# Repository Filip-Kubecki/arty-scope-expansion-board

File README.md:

<!-- markdownlint-disable MD013 MD060 -->

# Two-Channel Scope Expansion Board for Arty A7

KiCad design of an analog shield for the Digilent Arty A7 100T. The board plugs into the Pmod connectors and, together with the FPGA design, forms a two-channel digital oscilloscope.

## Hardware

- **Host board:** Digilent Arty A7 100T (connected via Pmod headers)
- **ADC:** AD9288-100 (dual 8-bit, 100 MS/s)
- **PGA:** AD8370 (variable gain amplifier)
- **DAC:** MCP4822 (DC offset)
- **EDA:** KiCad 10.0

## Related repositories

- FPGA design: [arty-scope-hdl](https://github.com/Filip-Kubecki/arty-scope-hdl)

## Repository structure

```
hardware/      KiCad project (schematic, PCB, project-local libraries)
  libs/        custom symbols, footprints and 3D models
docs/          notes, datasheets, pinout and block diagram
fab/           fabrication outputs - Gerbers, drill, BOM, pick&place (git-ignored, see Releases)
```

## Getting started

Clone the repository:

```bash
git clone https://github.com/Filip-Kubecki/arty-scope-expansion-board.git
cd arty-scope-expansion-board
```

Open `hardware/arty-scope-expansion-board.kicad_pro` in KiCad. Project-local libraries are referenced through `sym-lib-table` and `fp-lib-table`, so no manual setup is needed.

### Generating fabrication files

Fabrication outputs are not stored in git. To generate them:

1. Open the PCB in the PCB Editor.
2. Run **File → Fabrication Outputs → Gerbers** and **Drill Files**, writing to `fab/`.
3. Export BOM and placement files from the Schematic and PCB Editors if needed.

Ready-to-order packages for tagged versions are attached to [GitHub Releases](https://github.com/Filip-Kubecki/arty-scope-expansion-board/releases).

## Status

Work in progress.

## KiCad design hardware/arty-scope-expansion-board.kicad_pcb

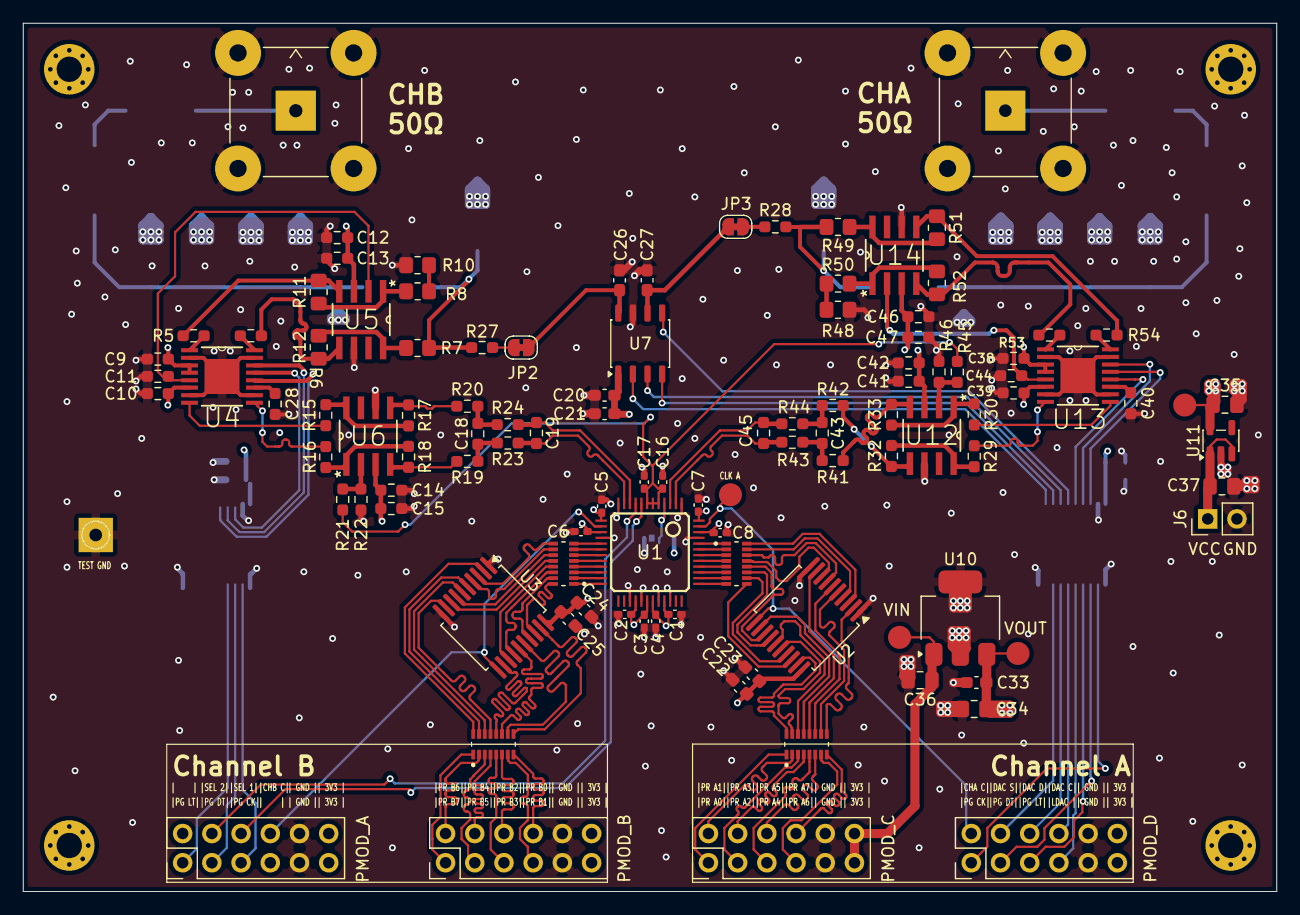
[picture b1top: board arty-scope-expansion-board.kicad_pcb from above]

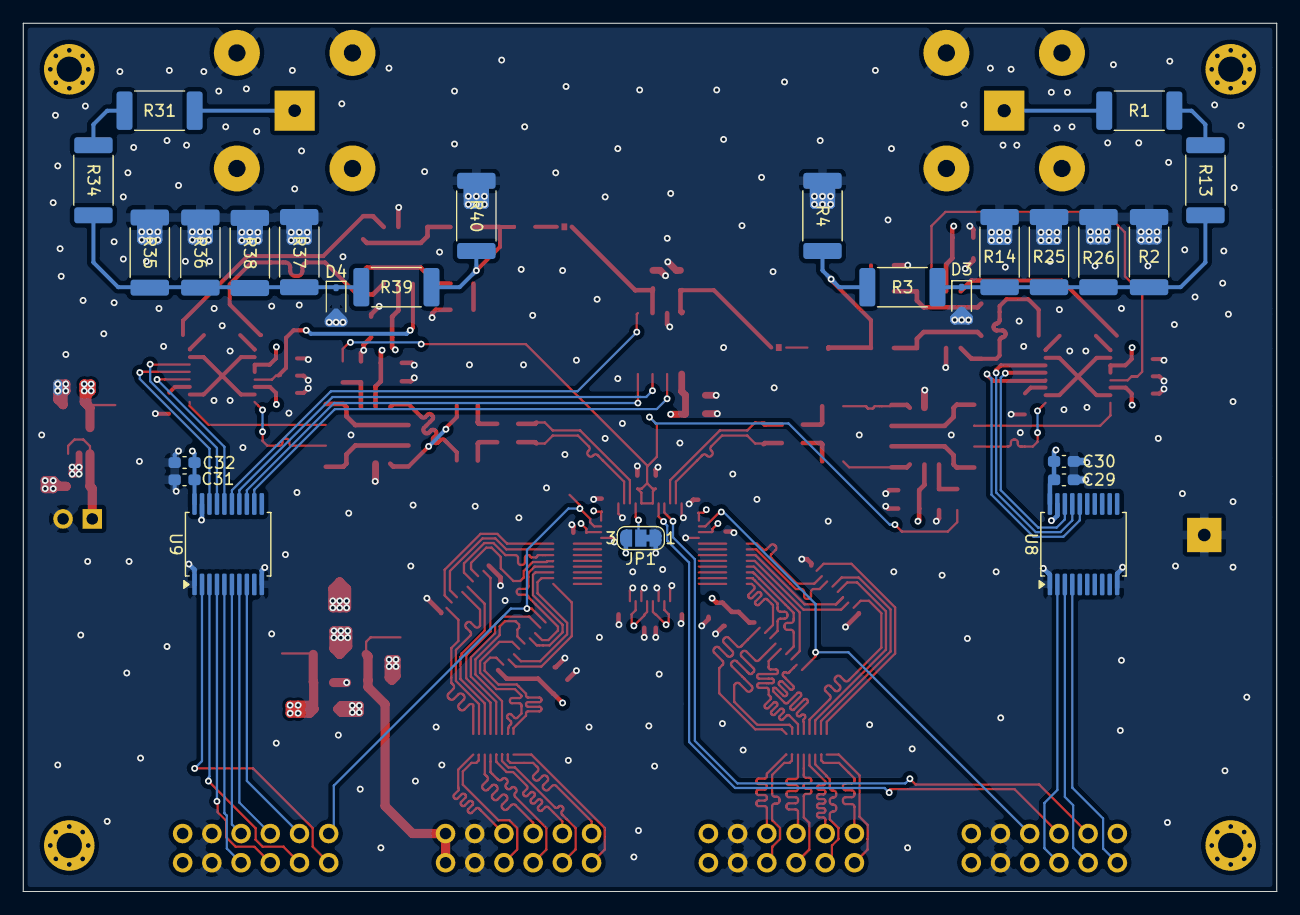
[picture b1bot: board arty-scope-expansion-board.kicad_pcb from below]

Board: 4 copper layers, 109.0 x 75.5 mm, 129 parts (25 on the bottom side), 147 nets.

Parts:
C1, C2, C3, C4, C5, C6, C7, C8, C16, C17: 100n; C_0402_1005Metric_Pad0.74x0.62mm_HandSolder
C9, C13, C14, C38, C41, C46: 100n; R_0603_1608Metric_Pad0.98x0.95mm_HandSolder
C10, C11, C28, C39, C40, C44: 1n; R_0603_1608Metric_Pad0.98x0.95mm_HandSolder
C12, C15, C42, C47: 10u; R_0603_1608Metric_Pad0.98x0.95mm_HandSolder
C18, C43: 47p; R_0603_1608Metric_Pad0.98x0.95mm_HandSolder
C19, C45: 10p; R_0603_1608Metric_Pad0.98x0.95mm_HandSolder
C20, C23, C25, C29, C31, C33: 100n; C_0603_1608Metric_Pad1.08x0.95mm_HandSolder
C21, C22, C24, C30, C32: 10u; C_0603_1608Metric_Pad1.08x0.95mm_HandSolder
C26, C27: 1n; C_0603_1608Metric_Pad1.08x0.95mm_HandSolder
C34, C35, C37: 1u; C_0805_2012Metric_Pad1.18x1.45mm_HandSolder
C36: 4u7; C_0805_2012Metric_Pad1.18x1.45mm_HandSolder
D3, D4: CDSOD323-T24C; D_SOD-323
J1: PMOD_A; PinHeader_2x06_P2.54mm_Vertical
J2: PMOD_B; PinHeader_2x06_P2.54mm_Vertical
J3: PMOD_C; PinHeader_2x06_P2.54mm_Vertical
J4: PMOD_D; PinHeader_2x06_P2.54mm_Vertical
J5, J7: Conn_Coaxial; BNC_TEConnectivity_1478035_Horizontal
J6: Conn_01x02_Pin; PinHeader_1x02_P2.54mm_Vertical
JP1: DFS Select; SolderJumper-3_P1.3mm_Bridged12_RoundedPad1.0x1.5mm_NumberL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
JP2, JP3: Jumper_2_Bridged; SolderJumper-2_P1.3mm_Bridged_RoundedPad1.0x1.5mm
R1, R13, R31, R34: 11; R_2512_6332Metric_Pad1.40x3.35mm_HandSolder
R2, R14, R25, R26, R35, R36, R37, R38: 222; R_2512_6332Metric_Pad1.40x3.35mm_HandSolder
R3, R39: 499; R_2512_6332Metric_Pad1.40x3.35mm_HandSolder
R4, R40: 55.6; R_2512_6332Metric_Pad1.40x3.35mm_HandSolder
R5, R6, R19, R20, R41, R42, R53, R54: 100; R_0603_1608Metric_Pad0.98x0.95mm_HandSolder
R7, R8, R11, R12, R49, R50, R51, R52: 499; R_0805_2012Metric_Pad1.20x1.40mm_HandSolder
R10, R48: 27.8; R_0805_2012Metric_Pad1.20x1.40mm_HandSolder
R15, R16, R17, R18, R29, R30, R32, R33: 499; R_0603_1608Metric_Pad0.98x0.95mm_HandSolder
R21, R45: 2.61k; R_0603_1608Metric_Pad0.98x0.95mm_HandSolder
R22, R46: 10k; R_0603_1608Metric_Pad0.98x0.95mm_HandSolder
R23, R24, R43, R44: 49.9; R_0603_1608Metric_Pad0.98x0.95mm_HandSolder
R27, R28: 20k; R_0603_1608Metric_Pad0.98x0.95mm_HandSolder
R_Pack_ADC_Side_A1: 51; RESCAXE50P380X160X55-16N
R_Pack_ADC_Side_B1: 51; RESCAXE50P380X160X55-16N
R_Pack_PMOD_Side_A1: 51; RESCAXE50P380X160X55-16N
R_Pack_PMOD_Side_B1: 51; RESCAXE50P380X160X55-16N
U1: AD9288; LQFP48
U2, U3: 74LS374; SSOP-20_5.3x7.2mm_P0.65mm
U4, U13: AD8370AREZ-RL7; SOP65P640X120-17N
U5, U6, U12, U14: AD8132ARZ; SOIC127P600X175-8N
U7: MCP4822; JEITA_SOIC-8_3.9x4.9mm_P1.27mm
U8, U9: 74AHCT541; SSOP-20_5.3x7.2mm_P0.65mm
U10: MCP1826S; SOT-223-3_TabPin2
U11: MIC5504-3.3YM5; SOT-23-5

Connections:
+3.3VCC: C1.1, C2.1, C3.1, C4.1, C5.1, C6.1, C7.1, C8.1, C22.1, C23.1, C24.1, C25.1, C33.1, C34.1, JP1.3 (B), U1.13 (VD@1), U1.15 (VDD@1), U1.28 (VDD@2), U1.30 (VD@2), U1.31 (VD@3), U1.33 (VDD@3), U1.46 (VDD@4), U1.48 (VD@4), U2.20 (VCC), U3.20 (VCC), U10.3 (VO)
+5VCC: C9.2, C10.2, C12.2, C13.2, C14.2, C15.2, C20.2, C21.2, C29.2, C30.2, C31.2, C32.2, C35.1, C38.2, C39.2, C41.2, C42.2, C46.2, C47.2, U4.3 (VCCI), U4.4 (PWUP), U4.6 (VCCO_2), U5.3 (V+), U6.3 (V+), U7.1 (Vdd), U8.20 (VCC), U9.20 (VCC), U11.5 (VOUT), U12.3 (V+), U13.3 (VCCI), U13.4 (PWUP), U13.6 (VCCO_2), U14.3 (V+)
/Root/ADC_DATA_A0: R_Pack_ADC_Side_A1.8 (R8.1), U1.37 (D0A)
/Root/ADC_DATA_A1: R_Pack_ADC_Side_A1.7 (R7.1), U1.38 (D1A)
/Root/ADC_DATA_A2: R_Pack_ADC_Side_A1.6 (R6.1), U1.39 (D2A)
/Root/ADC_DATA_A3: R_Pack_ADC_Side_A1.5 (R5.1), U1.40 (D3A)
/Root/ADC_DATA_A4: R_Pack_ADC_Side_A1.4 (R4.1), U1.41 (D4A)
/Root/ADC_DATA_A5: R_Pack_ADC_Side_A1.3 (R3.1), U1.42 (D5A)
/Root/ADC_DATA_A6: R_Pack_ADC_Side_A1.2 (R2.1), U1.43 (D6A)
/Root/ADC_DATA_A7: R_Pack_ADC_Side_A1.1 (R1.1), U1.44 (D7A)
/Root/ADC_DATA_B0: R_Pack_ADC_Side_B1.1 (R1.1), U1.24 (D0B)
/Root/ADC_DATA_B1: R_Pack_ADC_Side_B1.2 (R2.1), U1.23 (D1B)
/Root/ADC_DATA_B2: R_Pack_ADC_Side_B1.3 (R3.1), U1.22 (D2B)
/Root/ADC_DATA_B3: R_Pack_ADC_Side_B1.4 (R4.1), U1.21 (D3B)
/Root/ADC_DATA_B4: R_Pack_ADC_Side_B1.5 (R5.1), U1.20 (D4B)
/Root/ADC_DATA_B5: R_Pack_ADC_Side_B1.6 (R6.1), U1.19 (D5B)
/Root/ADC_DATA_B6: R_Pack_ADC_Side_B1.7 (R7.1), U1.18 (D6B)
/Root/ADC_DATA_B7: R_Pack_ADC_Side_B1.8 (R8.1), U1.17 (D7B)
/Root/DFLOP_ADC_DATA_A0: R_Pack_ADC_Side_A1.9 (R8.2), U2.18 (D7)
/Root/DFLOP_ADC_DATA_A1: R_Pack_ADC_Side_A1.10 (R7.2), U2.17 (D6)
/Root/DFLOP_ADC_DATA_A2: R_Pack_ADC_Side_A1.11 (R6.2), U2.14 (D5)
/Root/DFLOP_ADC_DATA_A3: R_Pack_ADC_Side_A1.12 (R5.2), U2.13 (D4)
/Root/DFLOP_ADC_DATA_A4: R_Pack_ADC_Side_A1.13 (R4.2), U2.8 (D3)
/Root/DFLOP_ADC_DATA_A5: R_Pack_ADC_Side_A1.14 (R3.2), U2.7 (D2)
/Root/DFLOP_ADC_DATA_A6: R_Pack_ADC_Side_A1.15 (R2.2), U2.4 (D1)
/Root/DFLOP_ADC_DATA_A7: R_Pack_ADC_Side_A1.16 (R1.2), U2.3 (D0)
/Root/DFLOP_ADC_DATA_B0: R_Pack_ADC_Side_B1.16 (R1.2), U3.18 (D7)
/Root/DFLOP_ADC_DATA_B1: R_Pack_ADC_Side_B1.15 (R2.2), U3.17 (D6)
/Root/DFLOP_ADC_DATA_B2: R_Pack_ADC_Side_B1.14 (R3.2), U3.14 (D5)
/Root/DFLOP_ADC_DATA_B3: R_Pack_ADC_Side_B1.13 (R4.2), U3.13 (D4)
/Root/DFLOP_ADC_DATA_B4: R_Pack_ADC_Side_B1.12 (R5.2), U3.8 (D3)
/Root/DFLOP_ADC_DATA_B5: R_Pack_ADC_Side_B1.11 (R6.2), U3.7 (D2)
/Root/DFLOP_ADC_DATA_B6: R_Pack_ADC_Side_B1.10 (R7.2), U3.4 (D1)
/Root/DFLOP_ADC_DATA_B7: R_Pack_ADC_Side_B1.9 (R8.2), U3.3 (D0)
/Root/DFLOP_PMOD_DATA_A0: R_Pack_PMOD_Side_A1.16 (R1.2), U2.19 (O7)
/Root/DFLOP_PMOD_DATA_A1: R_Pack_PMOD_Side_A1.15 (R2.2), U2.16 (O6)
/Root/DFLOP_PMOD_DATA_A2: R_Pack_PMOD_Side_A1.14 (R3.2), U2.15 (O5)
/Root/DFLOP_PMOD_DATA_A3: R_Pack_PMOD_Side_A1.13 (R4.2), U2.12 (O4)
/Root/DFLOP_PMOD_DATA_A4: R_Pack_PMOD_Side_A1.12 (R5.2), U2.9 (O3)
/Root/DFLOP_PMOD_DATA_A5: R_Pack_PMOD_Side_A1.11 (R6.2), U2.6 (O2)
/Root/DFLOP_PMOD_DATA_A6: R_Pack_PMOD_Side_A1.10 (R7.2), U2.5 (O1)
/Root/DFLOP_PMOD_DATA_A7: R_Pack_PMOD_Side_A1.9 (R8.2), U2.2 (O0)
/Root/DFLOP_PMOD_DATA_B0: R_Pack_PMOD_Side_B1.9 (R8.2), U3.19 (O7)
/Root/DFLOP_PMOD_DATA_B1: R_Pack_PMOD_Side_B1.10 (R7.2), U3.16 (O6)
/Root/DFLOP_PMOD_DATA_B2: R_Pack_PMOD_Side_B1.11 (R6.2), U3.15 (O5)
/Root/DFLOP_PMOD_DATA_B3: R_Pack_PMOD_Side_B1.12 (R5.2), U3.12 (O4)
/Root/DFLOP_PMOD_DATA_B4: R_Pack_PMOD_Side_B1.13 (R4.2), U3.9 (O3)
/Root/DFLOP_PMOD_DATA_B5: R_Pack_PMOD_Side_B1.14 (R3.2), U3.6 (O2)
/Root/DFLOP_PMOD_DATA_B6: R_Pack_PMOD_Side_B1.15 (R2.2), U3.5 (O1)
/Root/DFLOP_PMOD_DATA_B7: R_Pack_PMOD_Side_B1.16 (R1.2), U3.2 (O0)
/Root/PMOD_DATA_A0: J3.1, R_Pack_PMOD_Side_A1.1 (R1.1)
/Root/PMOD_DATA_A1: J3.2, R_Pack_PMOD_Side_A1.2 (R2.1)
/Root/PMOD_DATA_A2: J3.3, R_Pack_PMOD_Side_A1.3 (R3.1)
/Root/PMOD_DATA_A3: J3.4, R_Pack_PMOD_Side_A1.4 (R4.1)
/Root/PMOD_DATA_A4: J3.5, R_Pack_PMOD_Side_A1.5 (R5.1)
/Root/PMOD_DATA_A5: J3.6, R_Pack_PMOD_Side_A1.6 (R6.1)
/Root/PMOD_DATA_A6: J3.7, R_Pack_PMOD_Side_A1.7 (R7.1)
/Root/PMOD_DATA_A7: J3.8, R_Pack_PMOD_Side_A1.8 (R8.1)
/Root/PMOD_DATA_B0: J2.8, R_Pack_PMOD_Side_B1.8 (R8.1)
/Root/PMOD_DATA_B1: J2.7, R_Pack_PMOD_Side_B1.7 (R7.1)
/Root/PMOD_DATA_B2: J2.6, R_Pack_PMOD_Side_B1.6 (R6.1)
/Root/PMOD_DATA_B3: J2.5, R_Pack_PMOD_Side_B1.5 (R5.1)
/Root/PMOD_DATA_B4: J2.4, R_Pack_PMOD_Side_B1.4 (R4.1)
/Root/PMOD_DATA_B5: J2.3, R_Pack_PMOD_Side_B1.3 (R3.1)
/Root/PMOD_DATA_B6: J2.2, R_Pack_PMOD_Side_B1.2 (R2.1)
/Root/PMOD_DATA_B7: J2.1, R_Pack_PMOD_Side_B1.1 (R1.1)
AINA+: C19.2, R23.2, U1.11 (AINB)
AINA-: C19.1, R24.2, U1.10 (/AINB)
AINB+: C45.2, R43.2, U1.2 (AINA)
AINB-: C45.1, R44.2, U1.3 (/AINA)
CH_A_CLK: J4.2, U1.47 (ENCA), U2.11 (Cp)
CH_B_CLK: J1.8, U1.14 (ENCB), U3.11 (Cp)
DAC_A: R3.1, R4.1, R7.1, R27.1
DAC_B: R28.1, R39.1, R40.1, R49.1
DAC_CS_3.3V: J4.4, U9.8 (A6)
DAC_CS_5V: U7.2 (~CS), U9.12 (Y6)
DAC_LDAC_3.3V: J4.7, U9.5 (A3)
DAC_LDAC_5V: U7.5 (~LDAC), U9.15 (Y3)
DAC_SCK_3.3V: J4.8, U9.6 (A4)
DAC_SCK_5V: U7.3 (SCK), U9.14 (Y4)
DAC_SDI_3.3V: J4.6, U9.7 (A5)
DAC_SDI_5V: U7.4 (SDI), U9.13 (Y5)
GND: C1.2, C2.2, C3.2, C4.2, C5.2, C6.2, C7.2, C8.2, C9.1, C10.1, C11.1, C12.1, C13.1, C14.1, C15.1, C16.1, C17.1, C20.1, C21.1, C22.2, C23.2, C24.2, C25.2, C26.2, C27.2, C28.1, C29.1, C30.1, C31.1, C32.1, C33.2, C34.2, C35.2, C36.2, C37.2, C38.1, C39.1, C40.1, C41.1, C42.1, C44.1, C46.1, C47.1, D3.2 (A2), D4.2 (A2), J1.9, J1.10, J2.9, J2.10, J3.9, J3.10, J4.9, J4.10, J5.2 (Ext), J6.2, J7.2 (Ext), JP1.1 (A), R2.2, R4.2, R10.1, R14.2, R22.1, R25.2, R26.2, R35.2, R36.2, R37.2, R38.2, R40.2, R46.1, R48.1, U1.1 (GND@1), U1.12 (GND@2), U1.16 (GND@3), U1.27 (GND@4), U1.29 (GND@5), U1.32 (GND@6), U1.34 (GND@7), U1.45 (GND@8), U2.1 (OE), U2.10 (GND), U3.1 (OE), U3.10 (GND), U4.2 (ICOM_2), U4.7 (OCOM_2), U4.10 (OCOM), U4.15 (ICOM), U4.17 (EP), U5.6 (V-), U6.6 (V-), U7.7 (Vss), U8.1 (G1), U8.10 (GND), U8.19 (G2), U9.1 (G1), U9.10 (GND), U9.19 (G2), U10.2 (GND), U11.2 (GND), U12.6 (V-), U13.2 (ICOM_2), U13.7 (OCOM_2), U13.10 (OCOM), U13.15 (ICOM), U13.17 (EP), U14.6 (V-)
INHI_A: R5.2, U4.1 (INHI)
INHI_B: R53.2, U13.1 (INHI)
INLO_A: R6.2, U4.16 (INLO)
INLO_B: R54.2, U13.16 (INLO)
unnamed: C18.1, R20.2, R24.1
unnamed: C18.2, R19.2, R23.1
unnamed: C43.1, R42.2, R44.1
unnamed: C43.2, R41.2, R43.1
unnamed: D3.1 (A1), R2.1, R3.2, R13.1, R14.1, R25.1, R26.1
unnamed: D4.1 (A1), R34.1, R35.1, R36.1, R37.1, R38.1, R39.2
unnamed: J5.1 (In), R1.2
unnamed: C37.1, J6.1, U11.1 (VIN), U11.3 (EN)
unnamed: J7.1 (In), R31.2
unnamed: JP1.2 (C), U1.4 (DFS)
unnamed: C26.1, JP2.1 (A), U7.8 (VA)
unnamed: JP2.2 (B), R27.2
unnamed: C27.1, JP3.1 (A), U7.6 (VB)
unnamed: JP3.2 (B), R28.2
unnamed: R1.1, R13.2
unnamed: R8.1, R10.2
unnamed: R31.1, R34.2
unnamed: R48.2, R50.1
unnamed: C28.2, U4.11 (VCCO)
unnamed: R7.2, R12.2, U5.8 (+IN)
unnamed: R5.1, R11.2, U5.4 (+OUT)
unnamed: R8.2, R11.1, U5.1 (-IN)
unnamed: R6.1, R12.1, U5.5 (-OUT)
unnamed: R15.2, R17.2, U6.8 (+IN)
unnamed: R18.2, R19.1, U6.4 (+OUT)
unnamed: R16.2, R18.1, U6.1 (-IN)
unnamed: R17.1, R20.1, U6.5 (-OUT)
unnamed: R29.2, R32.2, U12.8 (+IN)
unnamed: R33.2, R41.1, U12.4 (+OUT)
unnamed: R30.2, R33.1, U12.1 (-IN)
unnamed: R32.1, R42.1, U12.5 (-OUT)
unnamed: C40.2, U13.11 (VCCO)
unnamed: R49.2, R51.2, U14.8 (+IN)
unnamed: R52.2, R53.1, U14.4 (+OUT)
unnamed: R50.2, R52.1, U14.1 (-IN)
unnamed: R51.1, R54.1, U14.5 (-OUT)
OP_A+: R15.1, U4.8 (OPHI)
OP_A-: R16.1, U4.9 (OPLO)
OP_B+: R29.1, U13.8 (OPHI)
OP_B-: R30.1, U13.9 (OPLO)
PGA_CLK_A_3.3V: J1.5, U8.2 (A0)
PGA_CLK_A_5V: U4.13 (CLCK), U8.18 (Y0)
PGA_CLK_B_3.3V: J4.1, U9.2 (A0)
PGA_CLK_B_5V: U9.18 (Y0), U13.13 (CLCK)
PGA_DATA_A_3.3V: J1.3, U8.3 (A1)
PGA_DATA_A_5V: U4.14 (DATA), U8.17 (Y1)
PGA_DATA_B_3.3V: J4.3, U9.3 (A1)
PGA_DATA_B_5V: U9.17 (Y1), U13.14 (DATA)
PGA_LATCH_A_3.3V: J1.1, U8.4 (A2)
PGA_LATCH_A_5V: U4.12 (LTCH), U8.16 (Y2)
PGA_LATCH_B_3.3V: J4.5, U9.4 (A2)
PGA_LATCH_B_5V: U9.16 (Y2), U13.12 (LTCH)
REFOUT: C16.2, C17.2, R21.2, R45.2, U1.5 (REFINA), U1.6 (REFOUT), U1.7 (REFINB)
REFOUT_VOCM_A: R21.1, R22.2, U6.2 (VOCM)
REFOUT_VOCM_B: R45.1, R46.2, U12.2 (VOCM)
SEL1: J1.6, U1.8 (S1)
SEL2: J1.4, U1.9 (S2)
VIN_3.3V: C36.1, J3.11, J3.12, U10.1 (VI)
VOCM_A: C11.2, U4.5 (VOCM), U5.2 (VOCM)
VOCM_B: C44.2, U13.5 (VOCM), U14.2 (VOCM)
